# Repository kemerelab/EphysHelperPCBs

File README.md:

Electrode interface boards and other breakout-style boards useful for multichannel
electrophysiology experiments. For many designs, we use libraries (such as UsefulConnectors)
found in our library repository, https://github.com/kemerelab/EagleCADLibraries.git

Designs, code, data and other materials are offered under the Apache License 2.0. Please see
text in License.md.

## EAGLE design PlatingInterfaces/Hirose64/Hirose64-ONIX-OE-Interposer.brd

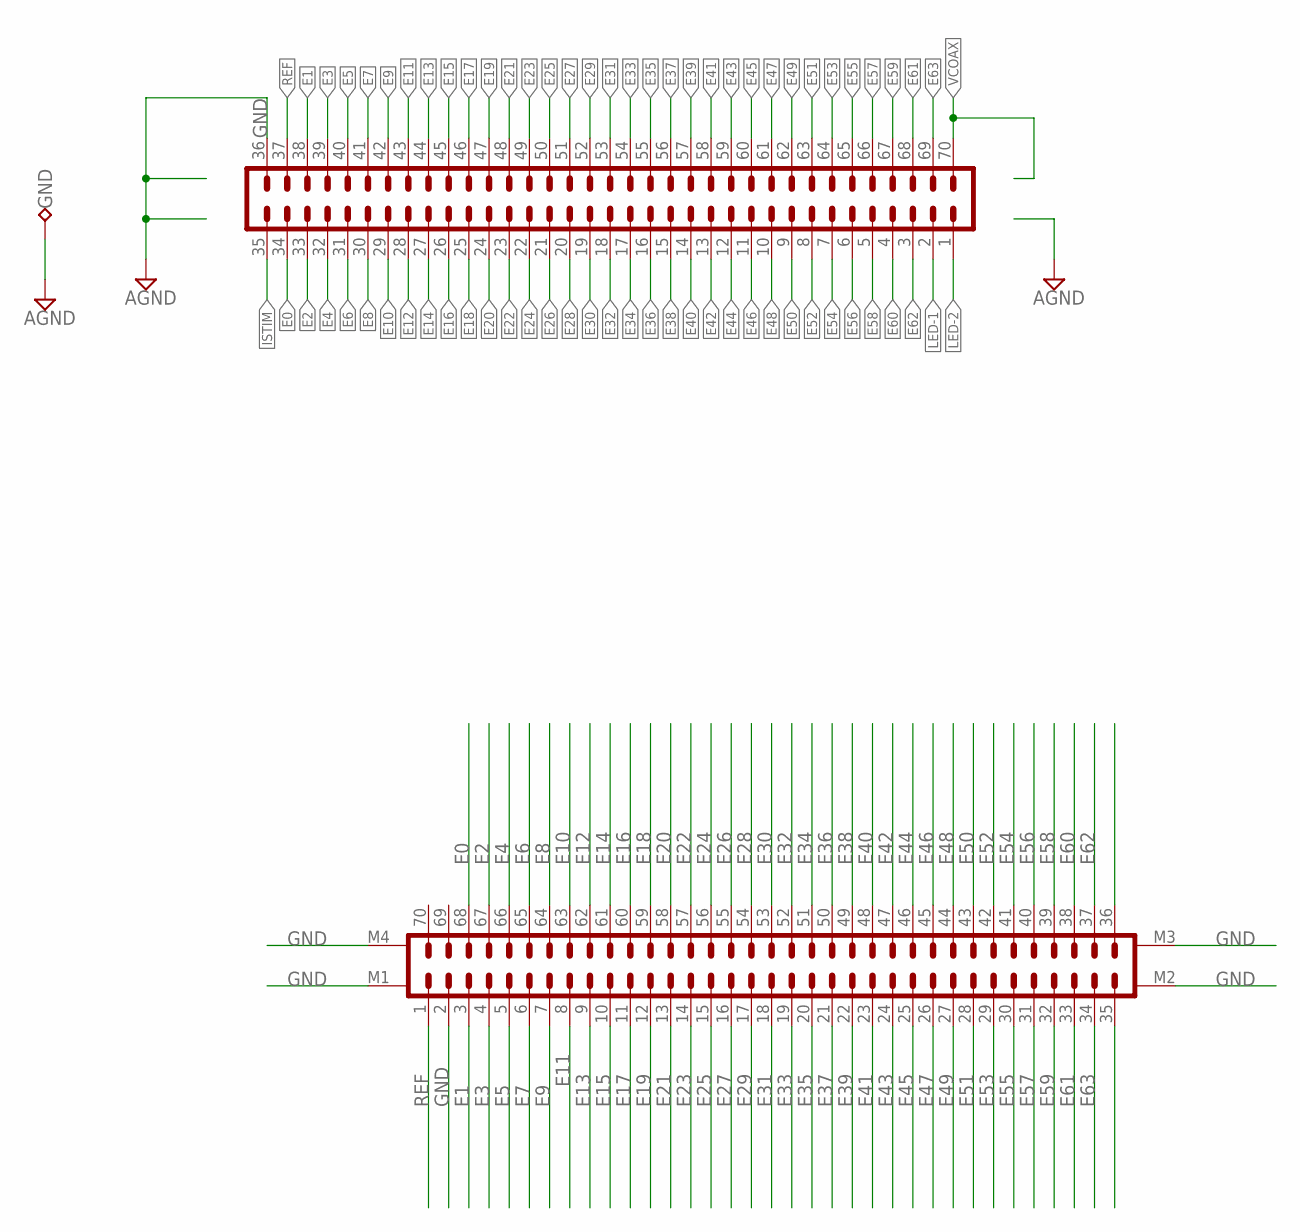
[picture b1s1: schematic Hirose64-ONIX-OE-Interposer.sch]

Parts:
GND: GND; TP07R
J3: DF40-REC; DDF40-70REC-LRG
J4: DF40C-70DP-0.4V(51); DF40-70HEAD-LESS-SILK

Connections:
E0: J3.34, J4.68
E1: J3.38, J4.3
E2: J3.33, J4.67
E3: J3.39, J4.4
E4: J3.32, J4.66
E5: J3.40, J4.5
E6: J3.31, J4.65
E7: J3.41, J4.6
E8: J3.30, J4.64
E9: J3.42, J4.7
E10: J3.29, J4.63
E11: J3.43, J4.8
E12: J3.28, J4.62
E13: J3.44, J4.9
E14: J3.27, J4.61
E15: J3.45, J4.10
E16: J3.26, J4.60
E17: J3.46, J4.11
E18: J3.25, J4.59
E19: J3.47, J4.12
E20: J3.24, J4.58
E21: J3.48, J4.13
E22: J3.23, J4.57
E23: J3.49, J4.14
E24: J3.22, J4.56
E25: J3.50, J4.15
E26: J3.21, J4.55
E27: J3.51, J4.16
E28: J3.20, J4.54
E29: J3.52, J4.17
E30: J3.19, J4.53
E31: J3.53, J4.18
E32: J3.18, J4.52
E33: J3.54, J4.19
E34: J3.17, J4.51
E35: J3.55, J4.20
E36: J3.16, J4.50
E37: J3.56, J4.21
E38: J3.15, J4.49
E39: J3.57, J4.22
E40: J3.14, J4.48
E41: J3.58, J4.23
E42: J3.13, J4.47
E43: J3.59, J4.24
E44: J3.12, J4.46
E45: J3.60, J4.25
E46: J3.11, J4.45
E47: J3.61, J4.26
E48: J3.10, J4.44
E49: J3.62, J4.27
E50: J3.9, J4.43
E51: J3.63, J4.28
E52: J3.8, J4.42
E53: J3.64, J4.29
E54: J3.7, J4.41
E55: J3.65, J4.30
E56: J3.6, J4.40
E57: J3.66, J4.31
E58: J3.5, J4.39
E59: J3.67, J4.32
E60: J3.4, J4.38
E61: J3.68, J4.33
E62: J3.3, J4.37
E63: J3.69, J4.34
ESTIM: J4.35
GND: GND.TP, J3.36, J4.2, J4.M1, J4.M2, J4.M3, J4.M4
ISTIM: J3.35
LED-1: J3.2
LED-2: J3.1
REF: J3.37, J4.1
REF1: J4.36
VCOAX: J3.70

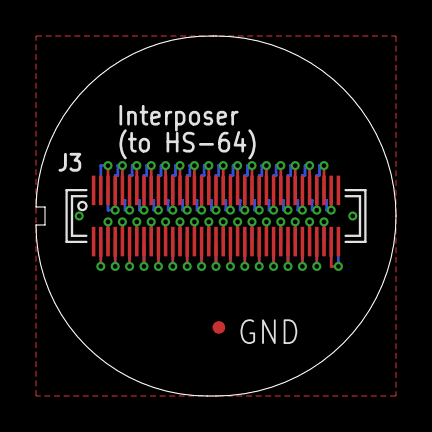
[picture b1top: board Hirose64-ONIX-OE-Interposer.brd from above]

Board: 2 copper layers, 20.0 x 20.0 mm, 3 parts (1 on the bottom side), 66 nets.

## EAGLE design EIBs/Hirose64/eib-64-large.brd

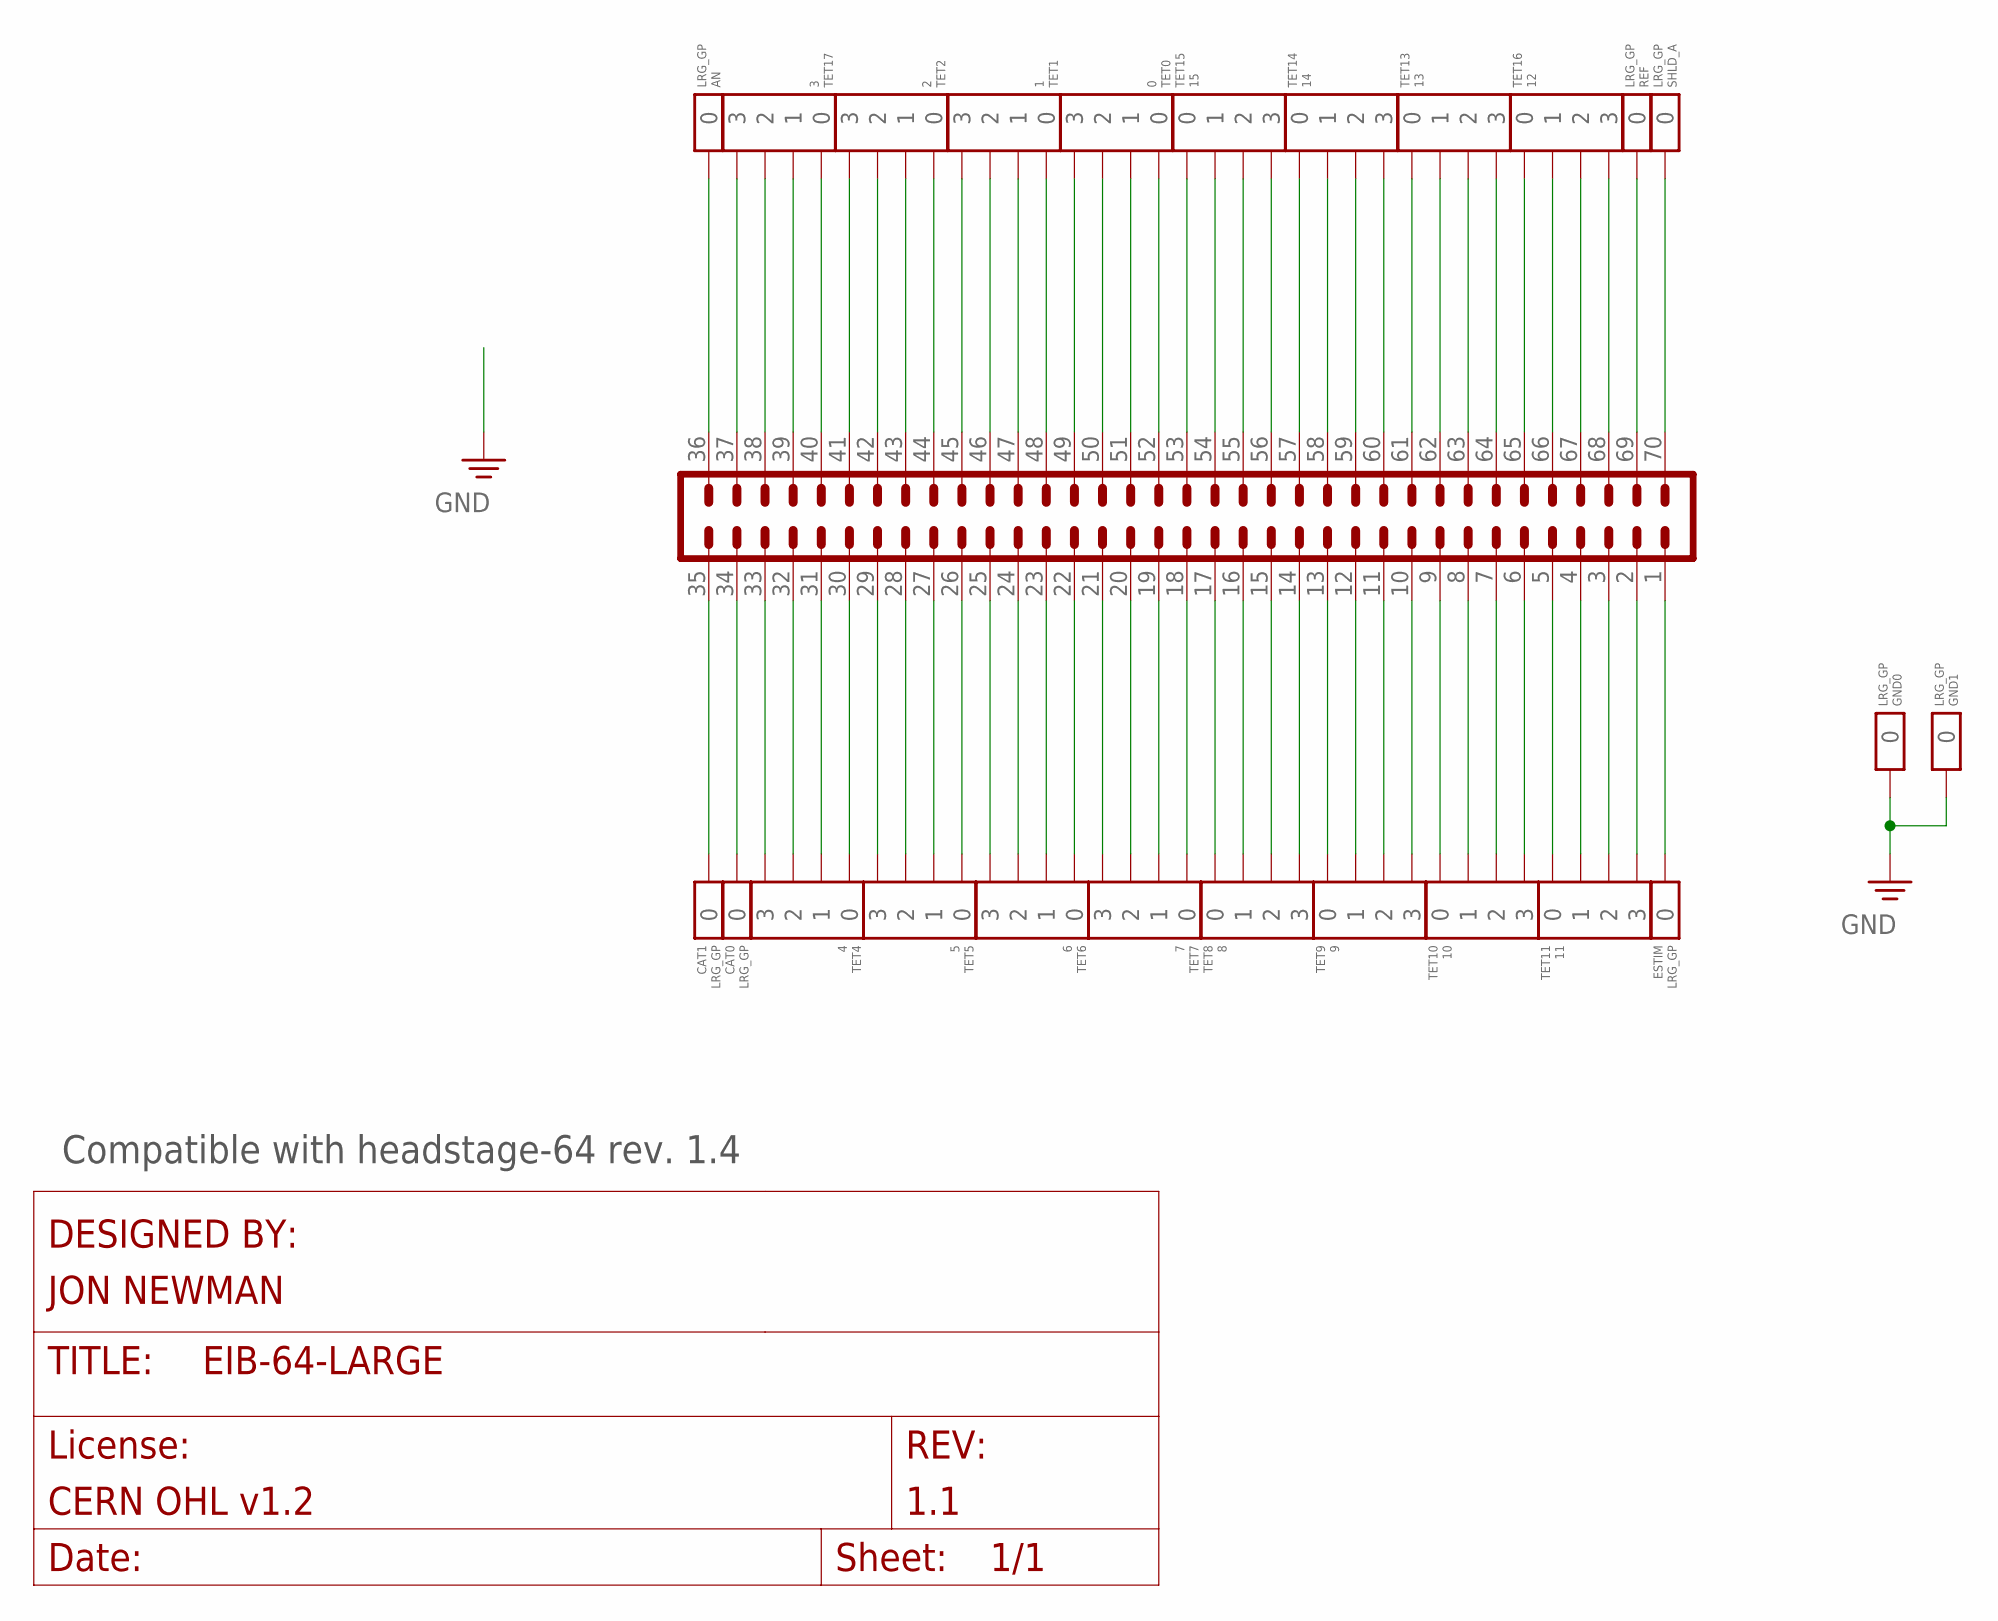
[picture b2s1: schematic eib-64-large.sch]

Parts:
AN: LRG_GP; GOLDPIN_0.5ID_0.7OD
CAT0, CAT1: LRG_GP; GOLDPIN_0.5ID_0.7OD
ESTIM: LRG_GP; GOLDPIN_0.5ID_0.7OD
GND0, GND1: LRG_GP; GOLDPIN_0.5ID_0.7OD
J1: DF40-REC; DDF40-70REC-LRG
REF: LRG_GP; GOLDPIN_0.5ID_0.7OD
SHLD_A: LRG_GP; GOLDPIN_0.5ID_0.7OD
TET0: 0; TETRODE_128_0.5ID_0.7OD
TET1: 1; TETRODE_128_0.5ID_0.7OD
TET2: 2; TETRODE_128_0.5ID_0.7OD
TET4: 4; TETRODE_128_0.5ID_0.7OD
TET5: 5; TETRODE_128_0.5ID_0.7OD
TET6: 6; TETRODE_128_0.5ID_0.7OD
TET7: 7; TETRODE_128_0.5ID_0.7OD
TET8: 8; TETRODE_128_0.5ID_0.7OD
TET9: 9; TETRODE_128_0.5ID_0.7OD
TET10: 10; TETRODE_128_0.5ID_0.7OD
TET11: 11; TETRODE_128_0.5ID_0.7OD
TET13: 13; TETRODE_128_0.5ID_0.7OD
TET14: 14; TETRODE_128_0.5ID_0.7OD
TET15: 15; TETRODE_128_0.5ID_0.7OD
TET16: 12; TETRODE_128_0.5ID_0.7OD
TET17: 3; TETRODE_128_0.5ID_0.7OD

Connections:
CAT0: CAT0.P$1, J1.34
CAT1: CAT1.P$1, J1.35
ESTIM: ESTIM.P$1, J1.1
GND: GND0.P$1, GND1.P$1
unnamed: AN.P$1, J1.36
unnamed: J1.69, REF.P$1
unnamed: J1.70, SHLD_A.P$1
unnamed: J1.51, TET0.1
unnamed: J1.52, TET0.0
unnamed: J1.50, TET0.2
unnamed: J1.49, TET0.3
unnamed: J1.47, TET1.1
unnamed: J1.48, TET1.0
unnamed: J1.46, TET1.2
unnamed: J1.45, TET1.3
unnamed: J1.43, TET2.1
unnamed: J1.44, TET2.0
unnamed: J1.42, TET2.2
unnamed: J1.41, TET2.3
unnamed: J1.62, TET13.1
unnamed: J1.61, TET13.0
unnamed: J1.63, TET13.2
unnamed: J1.64, TET13.3
unnamed: J1.58, TET14.1
unnamed: J1.57, TET14.0
unnamed: J1.59, TET14.2
unnamed: J1.60, TET14.3
unnamed: J1.54, TET15.1
unnamed: J1.53, TET15.0
unnamed: J1.55, TET15.2
unnamed: J1.56, TET15.3
unnamed: J1.66, TET16.1
unnamed: J1.65, TET16.0
unnamed: J1.67, TET16.2
unnamed: J1.68, TET16.3
unnamed: J1.39, TET17.1
unnamed: J1.5, TET11.0
unnamed: J1.4, TET11.1
unnamed: J1.3, TET11.2
unnamed: J1.2, TET11.3
unnamed: J1.40, TET17.0
unnamed: J1.38, TET17.2
unnamed: J1.37, TET17.3
unnamed: J1.33, TET4.3
unnamed: J1.32, TET4.2
unnamed: J1.31, TET4.1
unnamed: J1.30, TET4.0
unnamed: J1.29, TET5.3
unnamed: J1.28, TET5.2
unnamed: J1.27, TET5.1
unnamed: J1.26, TET5.0
unnamed: J1.25, TET6.3
unnamed: J1.24, TET6.2
unnamed: J1.23, TET6.1
unnamed: J1.22, TET6.0
unnamed: J1.21, TET7.3
unnamed: J1.20, TET7.2
unnamed: J1.19, TET7.1
unnamed: J1.18, TET7.0
unnamed: J1.17, TET8.0
unnamed: J1.16, TET8.1
unnamed: J1.15, TET8.2
unnamed: J1.14, TET8.3
unnamed: J1.13, TET9.0
unnamed: J1.12, TET9.1
unnamed: J1.11, TET9.2
unnamed: J1.10, TET9.3
unnamed: J1.9, TET10.0
unnamed: J1.8, TET10.1
unnamed: J1.7, TET10.2
unnamed: J1.6, TET10.3

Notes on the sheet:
Compatible with headstage-64 rev. 1.4

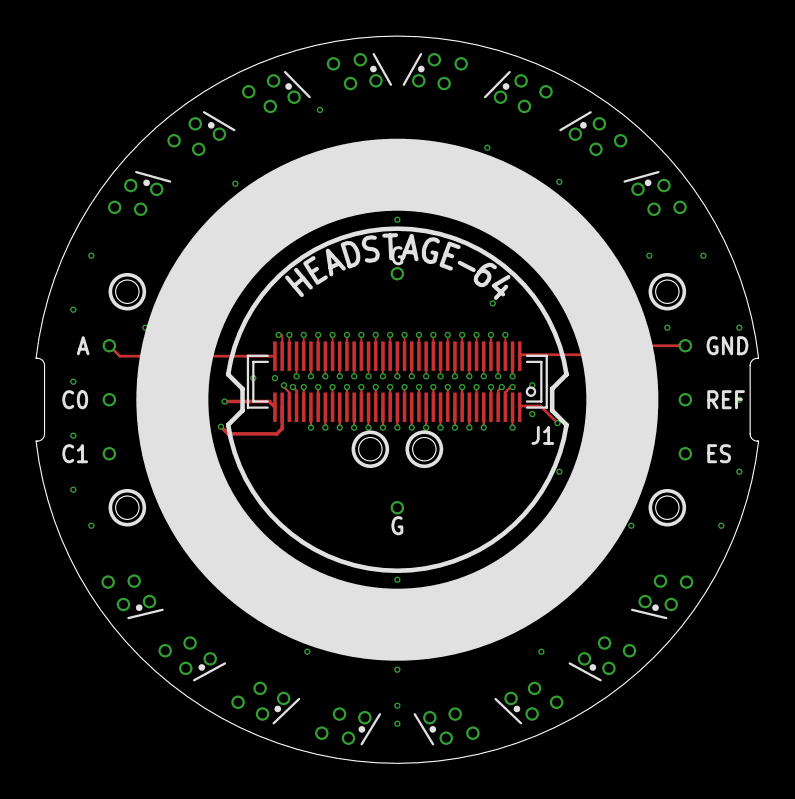
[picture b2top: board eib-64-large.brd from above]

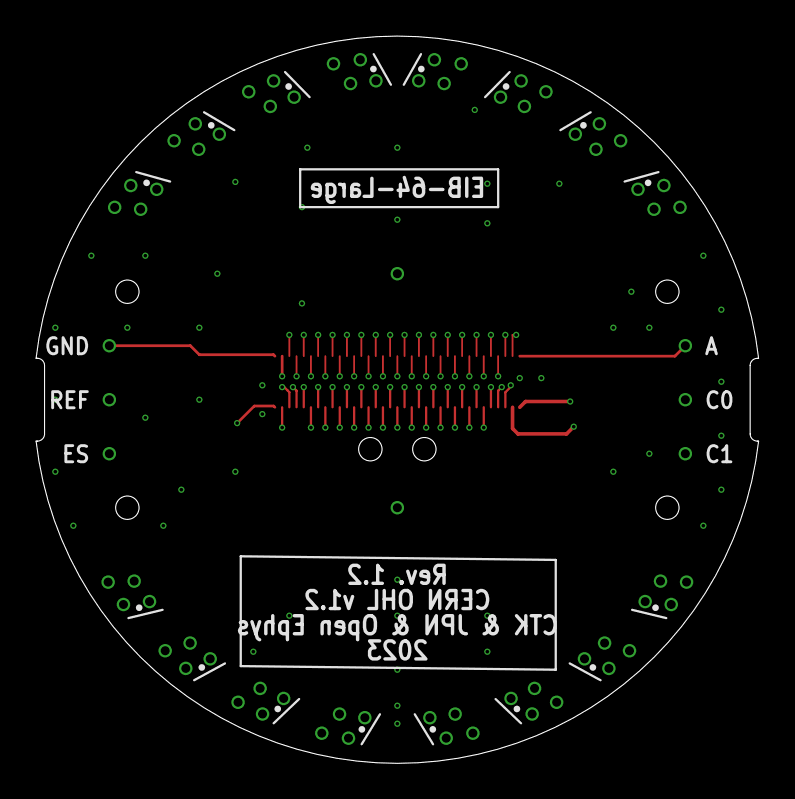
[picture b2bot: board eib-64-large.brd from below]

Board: 4 copper layers, 40.1 x 40.4 mm, 25 parts (8 on the bottom side), 71 nets.

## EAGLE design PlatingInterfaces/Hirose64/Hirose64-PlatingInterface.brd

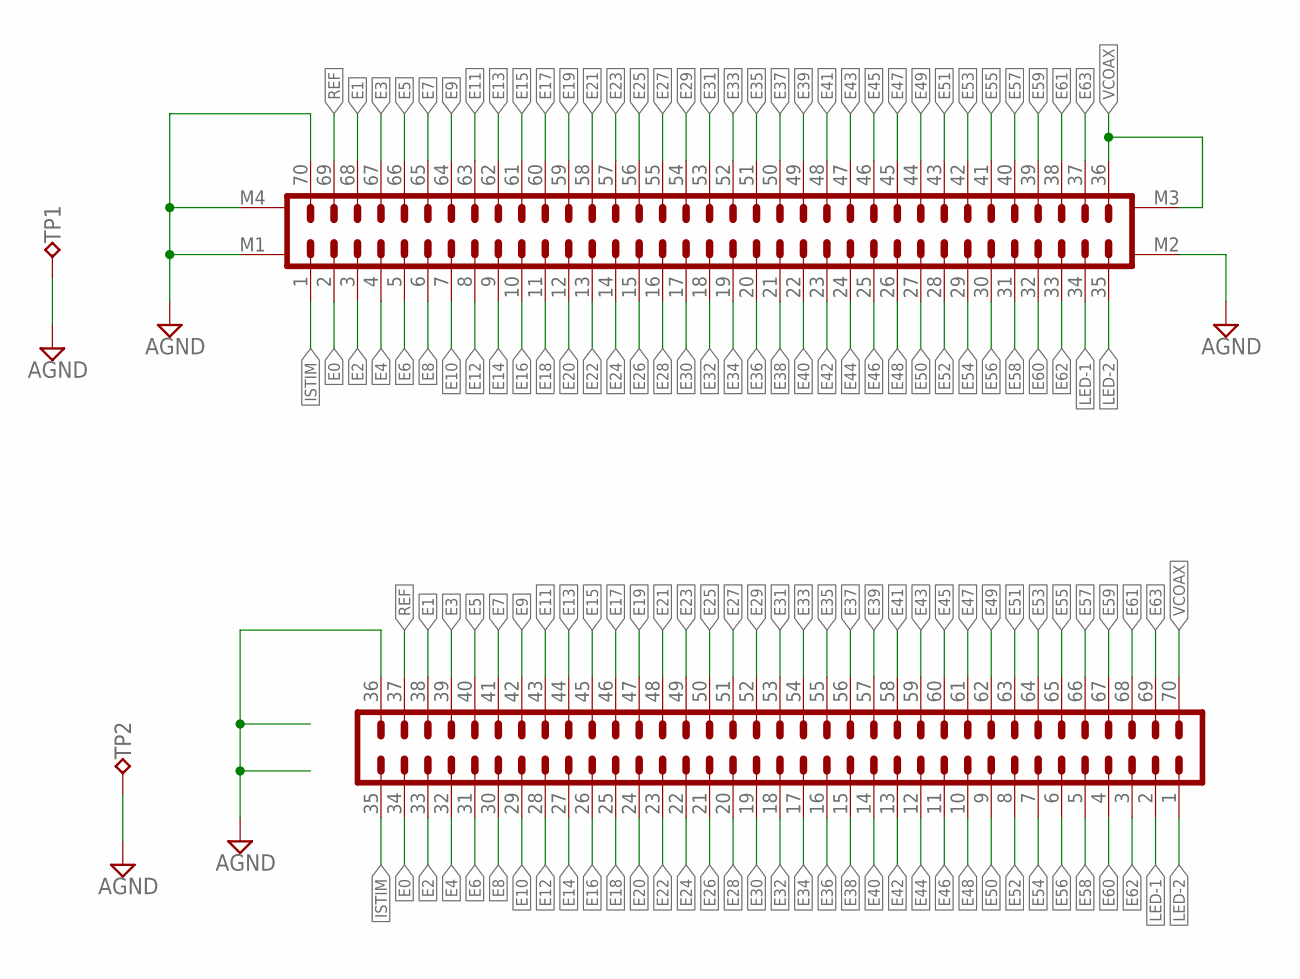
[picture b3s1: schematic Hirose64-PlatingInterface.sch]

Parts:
J1: DF40C-70DP-0.4V(51); DF40-70HEAD-LESS-SILK
J3: DF40-REC; DDF40-70REC-LRG
TP1, TP2: VCC; TP07R

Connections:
AGND: J1.70, J1.M1, J1.M2, J1.M4, J3.36, TP1.TP, TP2.TP
E0: J1.2, J3.34
E1: J1.68, J3.38
E2: J1.3, J3.33
E3: J1.67, J3.39
E4: J1.4, J3.32
E5: J1.66, J3.40
E6: J1.5, J3.31
E7: J1.65, J3.41
E8: J1.6, J3.30
E9: J1.64, J3.42
E10: J1.7, J3.29
E11: J1.63, J3.43
E12: J1.8, J3.28
E13: J1.62, J3.44
E14: J1.9, J3.27
E15: J1.61, J3.45
E16: J1.10, J3.26
E17: J1.60, J3.46
E18: J1.11, J3.25
E19: J1.59, J3.47
E20: J1.12, J3.24
E21: J1.58, J3.48
E22: J1.13, J3.23
E23: J1.57, J3.49
E24: J1.14, J3.22
E25: J1.56, J3.50
E26: J1.15, J3.21
E27: J1.55, J3.51
E28: J1.16, J3.20
E29: J1.54, J3.52
E30: J1.17, J3.19
E31: J1.53, J3.53
E32: J1.18, J3.18
E33: J1.52, J3.54
E34: J1.19, J3.17
E35: J1.51, J3.55
E36: J1.20, J3.16
E37: J1.50, J3.56
E38: J1.21, J3.15
E39: J1.49, J3.57
E40: J1.22, J3.14
E41: J1.48, J3.58
E42: J1.23, J3.13
E43: J1.47, J3.59
E44: J1.24, J3.12
E45: J1.46, J3.60
E46: J1.25, J3.11
E47: J1.45, J3.61
E48: J1.26, J3.10
E49: J1.44, J3.62
E50: J1.27, J3.9
E51: J1.43, J3.63
E52: J1.28, J3.8
E53: J1.42, J3.64
E54: J1.29, J3.7
E55: J1.41, J3.65
E56: J1.30, J3.6
E57: J1.40, J3.66
E58: J1.31, J3.5
E59: J1.39, J3.67
E60: J1.32, J3.4
E61: J1.38, J3.68
E62: J1.33, J3.3
E63: J1.37, J3.69
ISTIM: J1.1, J3.35
LED-1: J1.34, J3.2
LED-2: J1.35, J3.1
REF: J1.69, J3.37
VCOAX: J1.36, J1.M3, J3.70

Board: 2 copper layers, 4 parts (2 on the bottom side), 70 nets, no tracks yet.

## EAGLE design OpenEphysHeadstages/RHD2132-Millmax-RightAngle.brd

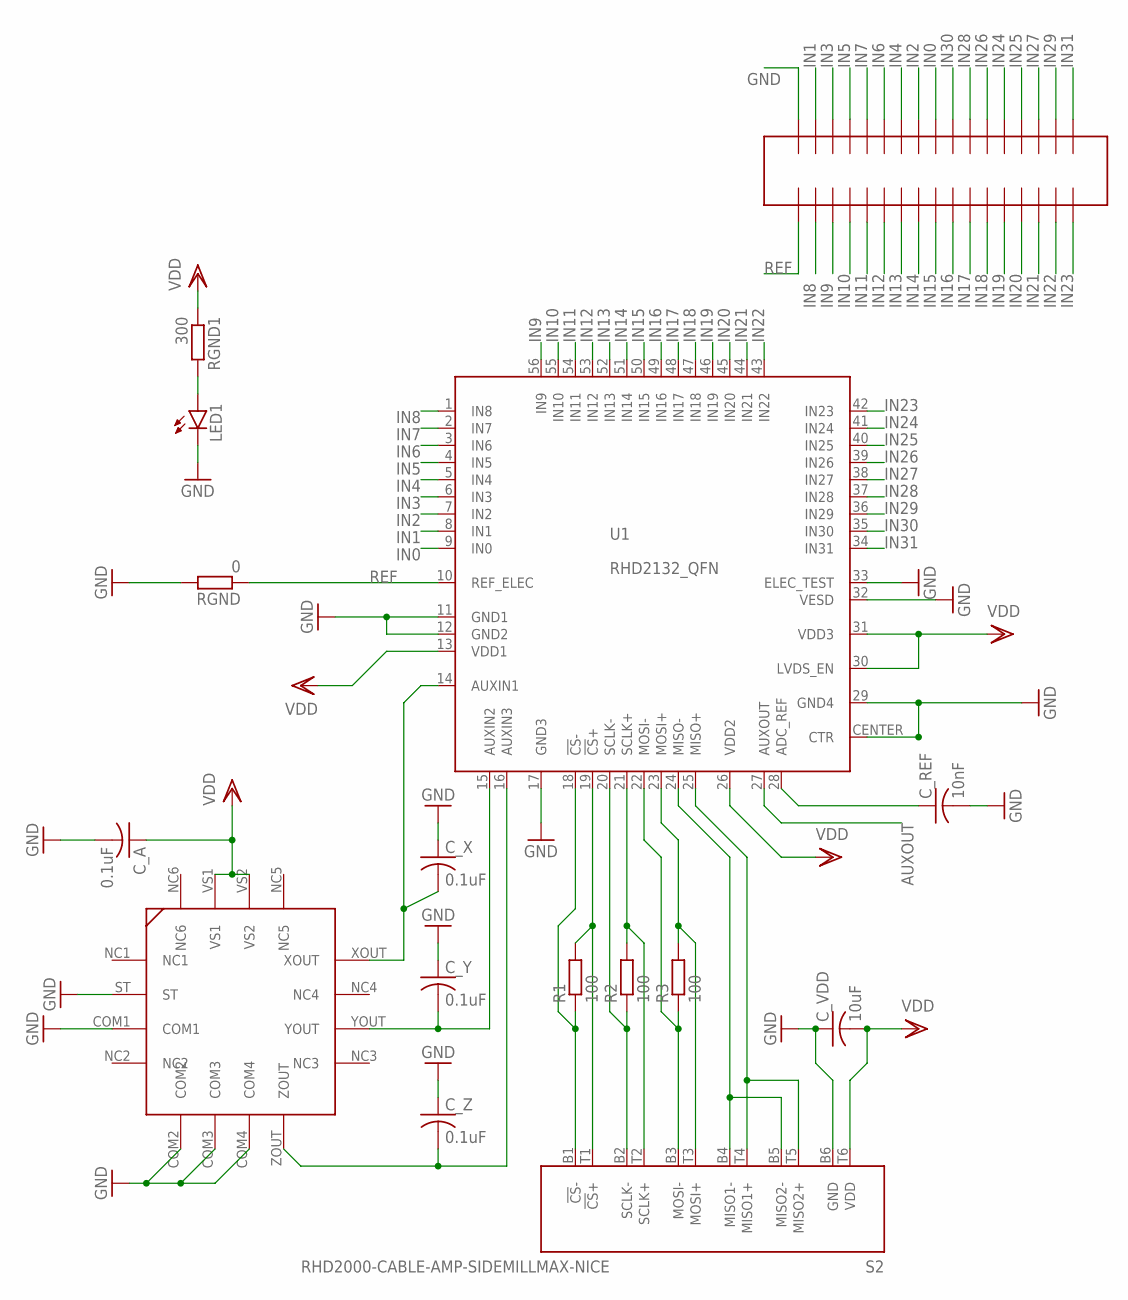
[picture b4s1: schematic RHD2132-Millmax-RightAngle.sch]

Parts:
C_A: 0.1uF; C0402K
C_REF: 10nF; C0402K
C_VDD: 10uF; C1206
C_X: 0.1uF; C0402K
C_Y: 0.1uF; C0402K
C_Z: 0.1uF; C0402K
LED1: LEDCHIPLED_0805; CHIPLED_0805
R1, R2, R3: 100; R0402
RGND: 0; R0402
RGND1: 300; R0402
S2: RHD2000-CABLE-AMP-SIDEMILLMAX-NICE; MILLMAX-12PIN-NICE
U1: RHD2132_QFN; QFN56_8_X_8_LARGE
U$1: ADXL335
U$2: FTSH-117BOARD-END; FTSH-117-END

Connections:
ADC_REF: C_REF.1, U1.28 (ADC_REF)
AUXOUT: U1.27 (AUXOUT)
CS+: R1.2, S2.T1 (!CS!+), U1.19 (!CS!+)
CS-: R1.1, S2.B1 (!CS!-), U1.18 (!CS!-)
GND: C_A.2, C_REF.2, C_VDD.1, C_X.1, C_Y.1, C_Z.1, LED1.C, RGND.2, S2.B6 (GND), U1.11 (GND1), U1.12 (GND2), U1.17 (GND3), U1.29 (GND4), U1.32 (VESD), U1.33 (ELEC_TEST), U1.CENTER (CTR), U$1.COM1, U$1.COM2, U$1.COM3, U$1.COM4, U$1.ST, U$2.P$34
IN0: U1.9 (IN0), U$2.P$26
IN1: U1.8 (IN1), U$2.P$33
IN2: U1.7 (IN2), U$2.P$27
IN3: U1.6 (IN3), U$2.P$32
IN4: U1.5 (IN4), U$2.P$28
IN5: U1.4 (IN5), U$2.P$31
IN6: U1.3 (IN6), U$2.P$29
IN7: U1.2 (IN7), U$2.P$30
IN8: U1.1 (IN8), U$2.P$2
IN9: U1.56 (IN9), U$2.P$3
IN10: U1.55 (IN10), U$2.P$4
IN11: U1.54 (IN11), U$2.P$5
IN12: U1.53 (IN12), U$2.P$6
IN13: U1.52 (IN13), U$2.P$7
IN14: U1.51 (IN14), U$2.P$8
IN15: U1.50 (IN15), U$2.P$9
IN16: U1.49 (IN16), U$2.P$10
IN17: U1.48 (IN17), U$2.P$11
IN18: U1.47 (IN18), U$2.P$12
IN19: U1.46 (IN19), U$2.P$13
IN20: U1.45 (IN20), U$2.P$14
IN21: U1.44 (IN21), U$2.P$15
IN22: U1.43 (IN22), U$2.P$16
IN23: U1.42 (IN23), U$2.P$17
IN24: U1.41 (IN24), U$2.P$22
IN25: U1.40 (IN25), U$2.P$21
IN26: U1.39 (IN26), U$2.P$23
IN27: U1.38 (IN27), U$2.P$20
IN28: U1.37 (IN28), U$2.P$24
IN29: U1.36 (IN29), U$2.P$19
IN30: U1.35 (IN30), U$2.P$25
IN31: U1.34 (IN31), U$2.P$18
MISO1+: S2.T4 (MISO1+), S2.T5 (MISO2+), U1.25 (MISO+)
MISO1-: S2.B4 (MISO1-), S2.B5 (MISO2-), U1.24 (MISO-)
MOSI+: R3.2, S2.T3 (MOSI+), U1.23 (MOSI+)
MOSI-: R3.1, S2.B3 (MOSI-), U1.22 (MOSI-)
unnamed: LED1.A, RGND1.2
REF: RGND.1, U1.10 (REF_ELEC), U$2.P$1
SCLK+: R2.2, S2.T2 (SCLK+), U1.21 (SCLK+)
SCLK-: R2.1, S2.B2 (SCLK-), U1.20 (SCLK-)
VDD: C_A.1, C_VDD.2, RGND1.1, S2.T6 (VDD), U1.13 (VDD1), U1.26 (VDD2), U1.30 (LVDS_EN), U1.31 (VDD3), U$1.VS1, U$1.VS2
XOUT: C_X.2, U1.14 (AUXIN1), U$1.XOUT
YOUT: C_Y.2, U1.15 (AUXIN2), U$1.YOUT
ZOUT: C_Z.2, U1.16 (AUXIN3), U$1.ZOUT

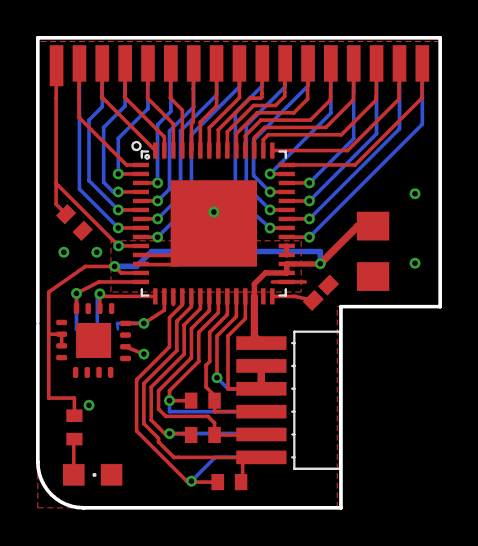
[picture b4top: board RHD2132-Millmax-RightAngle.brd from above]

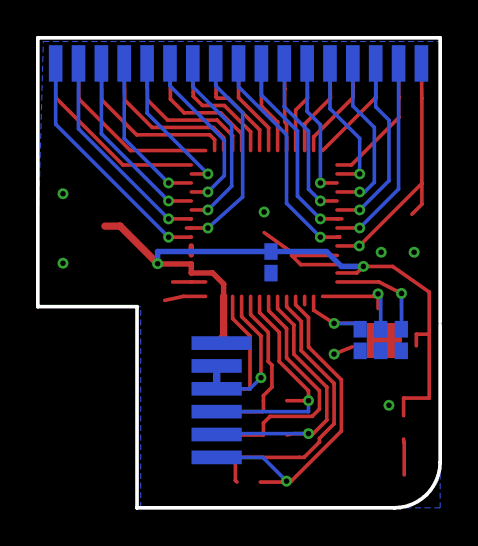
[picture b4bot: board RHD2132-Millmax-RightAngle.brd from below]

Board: 2 copper layers, 22.4 x 26.1 mm, 16 parts (4 on the bottom side), 48 nets.

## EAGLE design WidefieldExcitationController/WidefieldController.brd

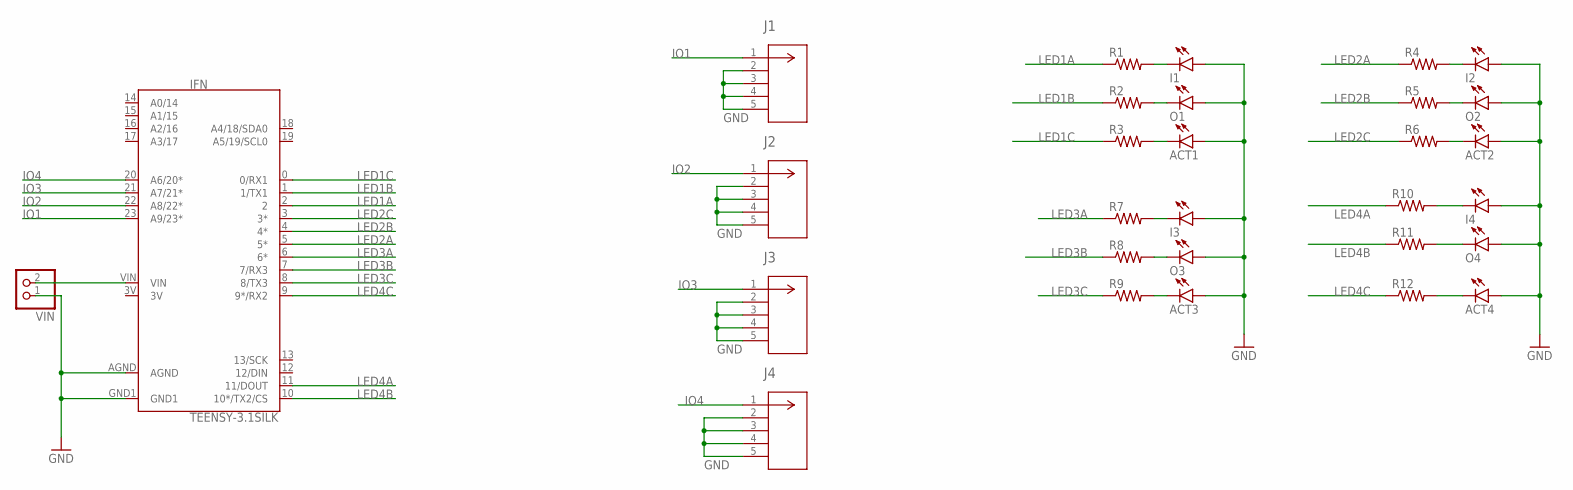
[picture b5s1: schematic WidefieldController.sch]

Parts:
ACT1, ACT2, ACT3, ACT4: LEDCHIPLED_0603; CHIPLED_0603
I1, I2, I3, I4: LEDCHIPLED_0603; CHIPLED_0603
IFN: TEENSY-3.1SILK; TEENSY-3.1
J1, J2, J3, J4: 5-1634503-1; CONN5_5-1634503-1_TEC
O1, O2, O3, O4: LEDCHIPLED_0603; CHIPLED_0603
R1, R2, R3, R4, R5, R6, R7, R8, R9, R10, R11, R12: R-US_R0603; R0603
VIN: PINHD-1X2; 1X02

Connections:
3V: IFN.3V
GND: ACT1.A, ACT2.A, ACT3.A, ACT4.A, I1.A, I2.A, I3.A, I4.A, IFN.AGND, IFN.GND1, J1.2, J1.3, J1.4, J1.5, J2.2, J2.3, J2.4, J2.5, J3.2, J3.3, J3.4, J3.5, J4.2, J4.3, J4.4, J4.5, O1.A, O2.A, O3.A, O4.A, VIN.1
IO1: IFN.23 (A9/23*), J1.1
IO2: IFN.22 (A8/22*), J2.1
IO3: IFN.21 (A7/21*), J3.1
IO4: IFN.20 (A6/20*), J4.1
LED1A: IFN.2, R1.1
LED1B: IFN.1 (1/TX1), R2.1
LED1C: IFN.0 (0/RX1), R3.1
LED2A: IFN.5 (5*), R4.1
LED2B: IFN.4 (4*), R5.1
LED2C: IFN.3 (3*), R6.1
LED3A: IFN.6 (6*), R7.1
LED3B: IFN.7 (7/RX3), R8.1
LED3C: IFN.8 (8/TX3), R9.1
LED4A: IFN.11 (11/DOUT), R10.1
LED4B: IFN.10 (10*/TX2/CS), R11.1
LED4C: IFN.9 (9*/RX2), R12.1
unnamed: I2.C, R4.2
unnamed: O2.C, R5.2
unnamed: ACT2.C, R6.2
unnamed: I4.C, R10.2
unnamed: O4.C, R11.2
unnamed: ACT4.C, R12.2
unnamed: IFN.VIN, VIN.2
unnamed: ACT3.C, R9.2
unnamed: O3.C, R8.2
unnamed: I3.C, R7.2
unnamed: I1.C, R1.2
unnamed: O1.C, R2.2
unnamed: ACT1.C, R3.2

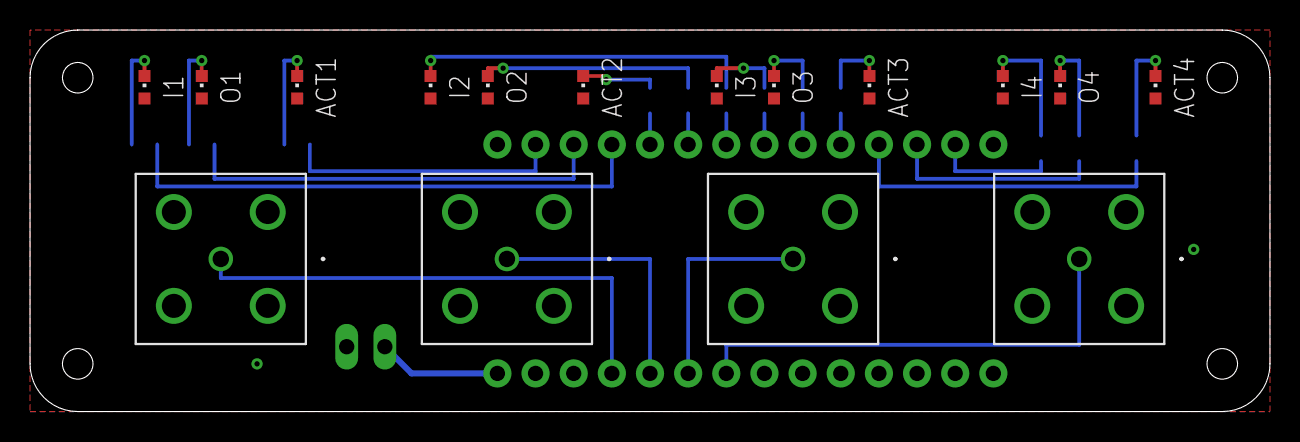
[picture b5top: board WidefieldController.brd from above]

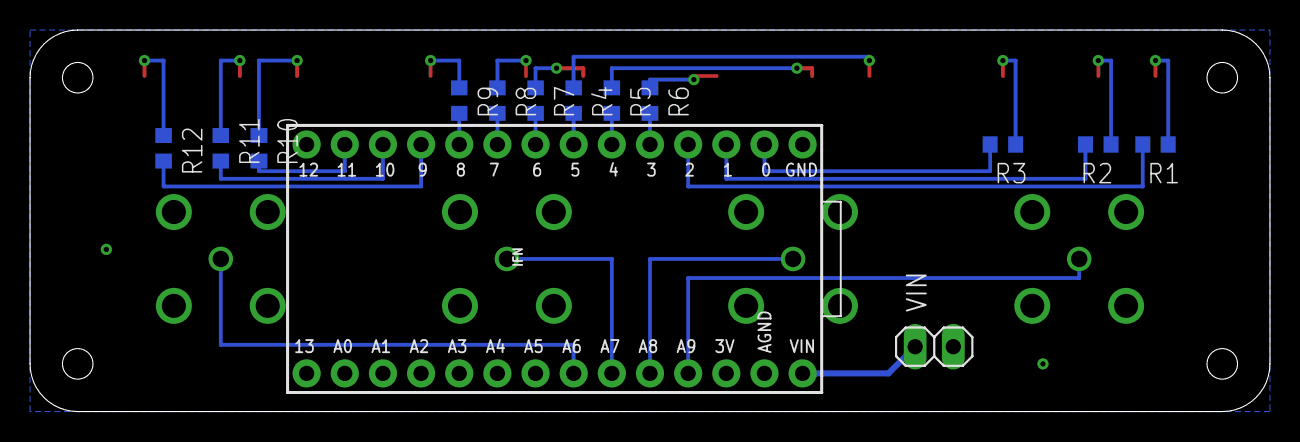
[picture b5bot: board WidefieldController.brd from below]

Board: 2 copper layers, 82.5 x 25.4 mm, 30 parts (14 on the bottom side), 30 nets.

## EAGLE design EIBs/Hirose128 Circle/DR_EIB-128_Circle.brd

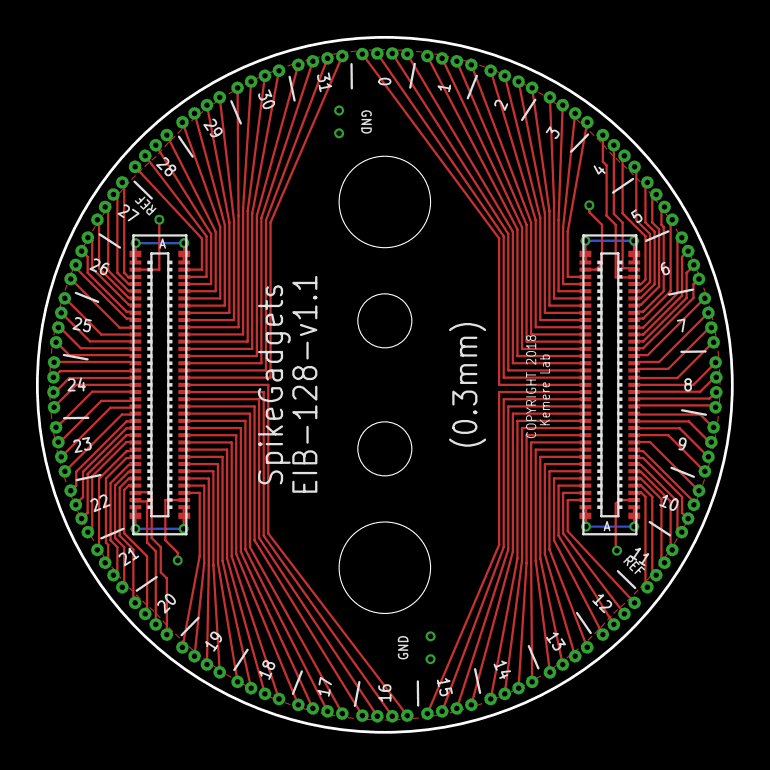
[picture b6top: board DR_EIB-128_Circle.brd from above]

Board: 2 copper layers, 38.6 x 38.6 mm, 42 parts (0 on the bottom side), 133 nets.

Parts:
0, 1, 2, 3, 4, 5, 6, 7, 8, 9, 10, 11, 12, 13, 14, 15, 16, 17, 18, 19, 20, 21, 22, 23, 24, 25, 26, 27, 28, 29, 30, 31: TETRODE_1.5IN_RADIUS0.3MM; TETRODE_1.5IN_RADIUS_0.3MM
U$1, U$2, U$4, U$5, U$6, U$7, U$8, U$9: TARRAYSHUTTLEHOLE
U$10, U$11: HIROSE-70PIN-HEADER-SEQUENTIAL; DF40C-70DP-0.4V

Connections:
GND: U$1.P$1, U$2.P$1, U$4.P$1, U$5.P$1, U$10.NC1, U$10.NC35, U$10.NC36, U$10.NC70, U$10.P$1, U$10.P$35, U$10.P$36, U$10.P$70, U$11.NC1, U$11.NC35, U$11.NC36, U$11.NC70, U$11.P$1, U$11.P$35, U$11.P$36, U$11.P$70
unnamed: U$9.P$1, U$11.P$69
unnamed: U$8.P$1, U$11.P$34
unnamed: U$7.P$1, U$10.P$69
unnamed: U$6.P$1, U$10.P$34
unnamed: 4.P$1, U$11.P$38
unnamed: 4.P$2, U$11.P$37
unnamed: 16.P$1, U$10.P$18
unnamed: 16.P$2, U$10.P$19
unnamed: 16.P$3, U$10.P$20
unnamed: 16.P$4, U$10.P$21
unnamed: 17.P$1, U$10.P$22
unnamed: 17.P$2, U$10.P$23
unnamed: 17.P$3, U$10.P$24
unnamed: 17.P$4, U$10.P$25
unnamed: 18.P$1, U$10.P$26
unnamed: 18.P$2, U$10.P$27
unnamed: 18.P$3, U$10.P$28
unnamed: 18.P$4, U$10.P$29
unnamed: 19.P$1, U$10.P$30
unnamed: 19.P$2, U$10.P$31
unnamed: 19.P$3, U$10.P$32
unnamed: 19.P$4, U$10.P$33
unnamed: 20.P$1, U$10.P$38
unnamed: 20.P$3, U$10.P$39
unnamed: 20.P$4, U$10.P$40
unnamed: 21.P$1, U$10.P$41
unnamed: 21.P$2, U$10.P$42
unnamed: 21.P$3, U$10.P$43
unnamed: 21.P$4, U$10.P$44
unnamed: 22.P$1, U$10.P$45
unnamed: 22.P$2, U$10.P$46
unnamed: 22.P$3, U$10.P$47
unnamed: 22.P$4, U$10.P$48
unnamed: 23.P$1, U$10.P$49
unnamed: 23.P$2, U$10.P$50
unnamed: 23.P$3, U$10.P$51
unnamed: 23.P$4, U$10.P$52
unnamed: 24.P$1, U$10.P$53
unnamed: 24.P$2, U$10.P$54
unnamed: 24.P$3, U$10.P$55
unnamed: 24.P$4, U$10.P$56
unnamed: 25.P$1, U$10.P$57
unnamed: 25.P$2, U$10.P$58
unnamed: 25.P$3, U$10.P$59
unnamed: 25.P$4, U$10.P$60
unnamed: 26.P$1, U$10.P$61
unnamed: 26.P$2, U$10.P$62
unnamed: 26.P$3, U$10.P$63
unnamed: 26.P$4, U$10.P$64
unnamed: 28.P$1, U$10.P$2
unnamed: 28.P$2, U$10.P$3
unnamed: 28.P$3, U$10.P$4
unnamed: 28.P$4, U$10.P$5
unnamed: 29.P$1, U$10.P$6
unnamed: 29.P$2, U$10.P$7
unnamed: 29.P$3, U$10.P$8
unnamed: 29.P$4, U$10.P$9
unnamed: 30.P$1, U$10.P$10
unnamed: 30.P$2, U$10.P$11
unnamed: 30.P$3, U$10.P$12
unnamed: 30.P$4, U$10.P$13
unnamed: 31.P$1, U$10.P$14
unnamed: 31.P$2, U$10.P$15
unnamed: 31.P$3, U$10.P$16
unnamed: 31.P$4, U$10.P$17
unnamed: 27.P$1, U$10.P$65
unnamed: 27.P$2, U$10.P$66
unnamed: 27.P$3, U$10.P$67
unnamed: 27.P$4, U$10.P$68
unnamed: 20.P$2, U$10.P$37
T6_1: 3.P$3, U$11.P$32
T6_2: 3.P$1, U$11.P$30
T6_3: 2.P$3, U$11.P$28
T6_4: 2.P$1, U$11.P$26
T7_1: 1.P$3, U$11.P$24
T7_2: 1.P$1, U$11.P$22
T7_3: 0.P$3, U$11.P$20
T7_4: 0.P$1, U$11.P$18
T8_1: 15.P$3, U$11.P$16
T8_2: 15.P$1, U$11.P$14
T8_3: 14.P$3, U$11.P$12
T8_4: 14.P$1, U$11.P$10
T9_1: 12.P$1, U$11.P$2
T9_2: 12.P$3, U$11.P$4
T9_3: 13.P$1, U$11.P$6
T9_4: 13.P$3, U$11.P$8
T10_1: 13.P$4, U$11.P$9
T10_2: 13.P$2, U$11.P$7
T10_3: 12.P$4, U$11.P$5
T10_4: 12.P$2, U$11.P$3
T11_1: 11.P$4, U$11.P$68
T11_2: 11.P$2, U$11.P$66
T11_3: 10.P$4, U$11.P$64
T11_4: 10.P$2, U$11.P$62
T12_1: 10.P$1, U$11.P$61
T12_2: 10.P$3, U$11.P$63
T12_3: 11.P$1, U$11.P$65
T12_4: 11.P$3, U$11.P$67
T13_1: 9.P$3, U$11.P$59
T13_2: 9.P$1, U$11.P$57
T13_3: 8.P$3, U$11.P$55
T13_4: 8.P$1, U$11.P$53
T14_1: 7.P$3, U$11.P$51
T14_2: 7.P$1, U$11.P$49
T14_3: 6.P$3, U$11.P$47
T14_4: 6.P$1, U$11.P$45
T15_1: 5.P$3, U$11.P$43
T15_2: 5.P$1, U$11.P$41
T15_3: 4.P$3, U$11.P$39
T21_1: 14.P$2, U$11.P$11
T21_2: 14.P$4, U$11.P$13
T21_3: 15.P$2, U$11.P$15
T21_4: 15.P$4, U$11.P$17
T22_1: 0.P$2, U$11.P$19
T22_2: 0.P$4, U$11.P$21
T22_3: 1.P$2, U$11.P$23
T22_4: 1.P$4, U$11.P$25
T23_1: 2.P$2, U$11.P$27
T23_2: 2.P$4, U$11.P$29
T23_3: 3.P$2, U$11.P$31
T23_4: 3.P$4, U$11.P$33
T24_2: 4.P$4, U$11.P$40
T24_3: 5.P$2, U$11.P$42
T24_4: 5.P$4, U$11.P$44
T25_1: 6.P$2, U$11.P$46
T25_2: 6.P$4, U$11.P$48
T25_3: 7.P$2, U$11.P$50
T25_4: 7.P$4, U$11.P$52
T26_1: 8.P$2, U$11.P$54
T26_2: 8.P$4, U$11.P$56
T26_3: 9.P$2, U$11.P$58
T26_4: 9.P$4, U$11.P$60

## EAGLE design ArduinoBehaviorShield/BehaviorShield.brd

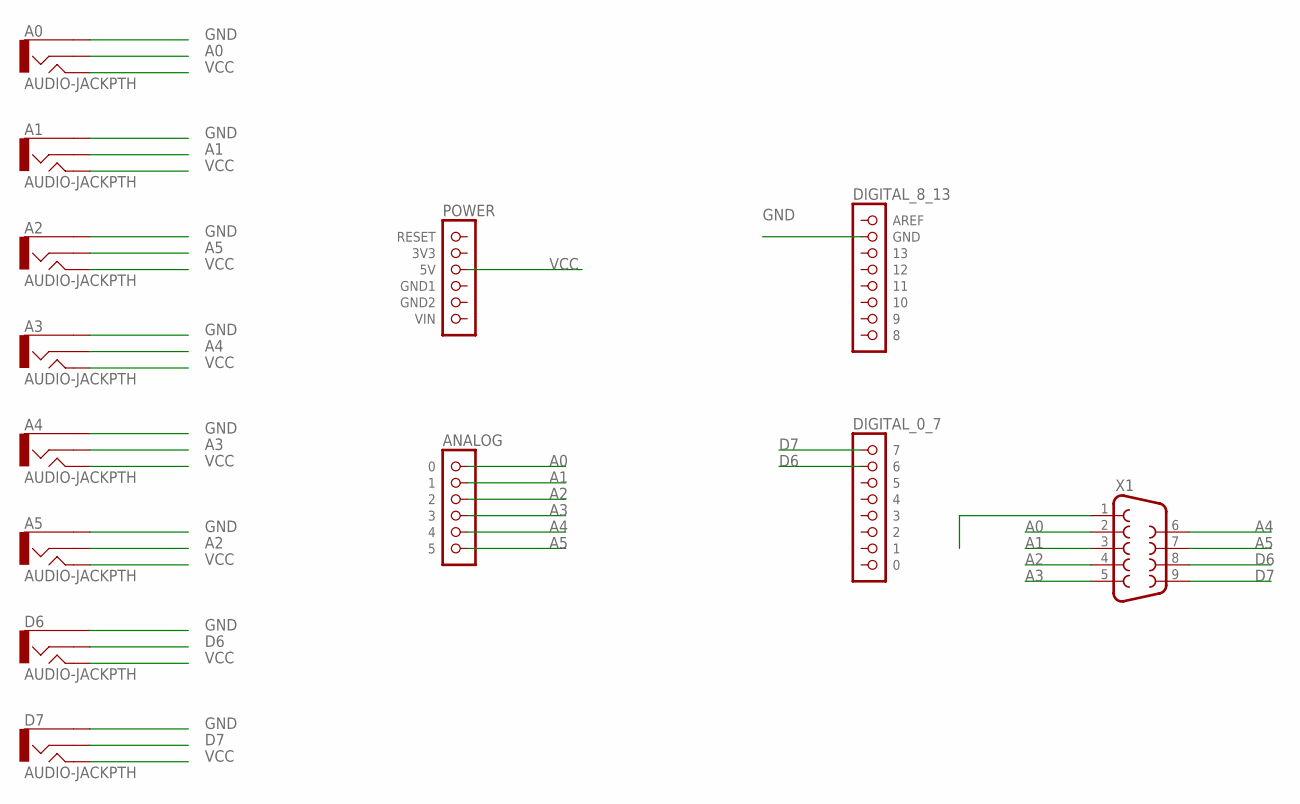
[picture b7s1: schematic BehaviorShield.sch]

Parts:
A0, A1, A2, A3, A4, A5: AUDIO-JACKPTH; AUDIO-JACK
D6, D7: AUDIO-JACKPTH; AUDIO-JACK
U$1: POWER; 1X06
U$2: ANALOG; 1X06
U$3: DIGITAL_0_7; 1X08
U$4: DIGITAL_8_13; 1X08
X1: F09HP

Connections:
A0: A0.2, U$2.1 (0), X1.2
A1: A1.2, U$2.2 (1), X1.3
A2: A5.2, U$2.3 (2), X1.4
A3: A4.2, U$2.4 (3), X1.5
A4: A3.2, U$2.5 (4), X1.6
A5: A2.2, U$2.6 (5), X1.7
D6: D6.2, U$3.2 (6), X1.8
D7: D7.2, U$3.1 (7), X1.9
GND: A0.1, A1.1, A2.1, A3.1, A4.1, A5.1, D6.1, D7.1, U$4.2 (GND), X1.1
VCC: A0.5, A1.5, A2.5, A3.5, A4.5, A5.5, D6.5, D7.5, U$1.3 (5V)

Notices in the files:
ArduinoBehaviorShield/BehaviorShield.brd:
(c) 2019 Caleb Kemere
EIBs/Hirose128 Circle/DR_EIB-128_Circle.brd:
COPYRIGHT 2018
EIBs/Hirose64/eib-64-large.brd:
CERN OHL v1.2
EIBs/Hirose64/eib-64-large.sch:
LICENSE: CERN OHL v1.2
OpenEphysHeadstages/RHD2132-Millmax-RightAngle.brd:
(C) 2016 Kemerelab.com
parts and their libraries:
SparkFun: Licensing: CC v3.0 Share-Alike You are welcome to use this library for commercial purposes.
SparkFun-Boards-TeensyMod: Licensing: Creative Commons ShareAlike 4.0 International - https://creativecommons.org/licenses/by-sa/4.0
